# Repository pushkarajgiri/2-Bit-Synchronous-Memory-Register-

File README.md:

# 2-Bit-Synchronous-Memory-Register-
74HC00N NAND gates to demonstrate Gated D-Latch architecture and synchronized volatile data storage.

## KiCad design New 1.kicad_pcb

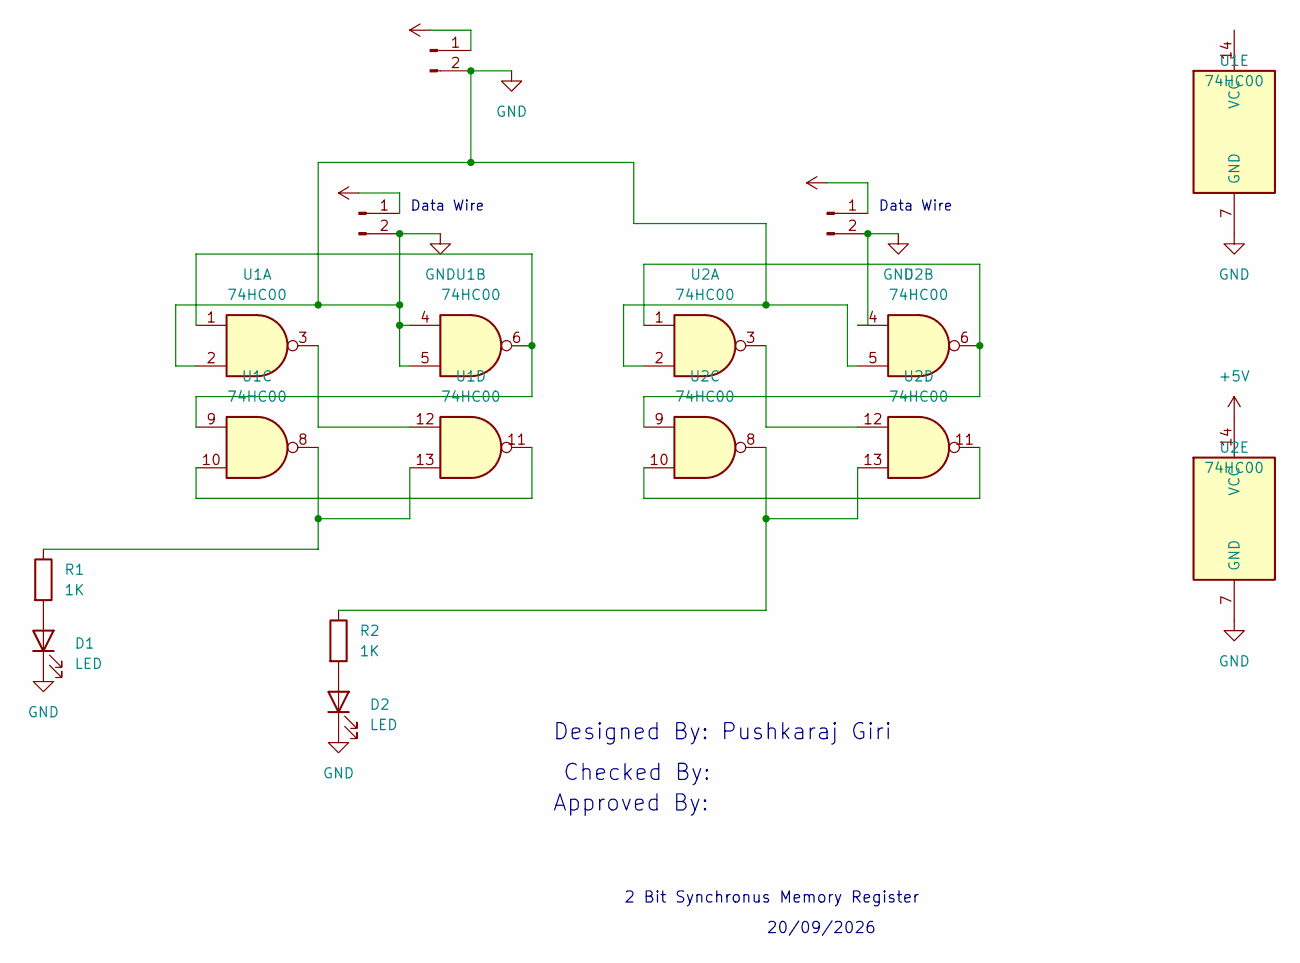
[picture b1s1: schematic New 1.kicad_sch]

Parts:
D1, D2: LED; LED_D5.0mm
J1, J2, J3: Conn_01x02_Pin; PinHeader_1x02_P2.54mm_Vertical
R1, R2: 1K; R_Axial_DIN0207_L6.3mm_D2.5mm_P10.16mm_Horizontal
U1, U2: 74HC00; DIP-14_W7.62mm

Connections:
+5V: J1.1, J2.1, J3.1, U2.14 (VCC)
GND: D1.1 (K), D2.1 (K), J1.2, J2.2, J3.2, U1.2, U1.4, U1.5, U1.7 (GND), U2.2, U2.4, U2.5, U2.7 (GND)
unnamed: D1.2 (A), R1.2
unnamed: D2.2 (A), R2.2
unnamed: R1.1, U1.8, U1.13
unnamed: R2.1, U2.8, U2.13
unnamed: U1.1, U1.6, U1.9
unnamed: U1.10, U1.11
unnamed: U1.3, U1.12
unnamed: U2.1, U2.6, U2.9
unnamed: U2.10, U2.11
unnamed: U2.3, U2.12

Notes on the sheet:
Data Wire
20/09/2026
2 Bit Synchronus Memory Register
Designed By: Pushkaraj Giri
Approved By:
Checked By:

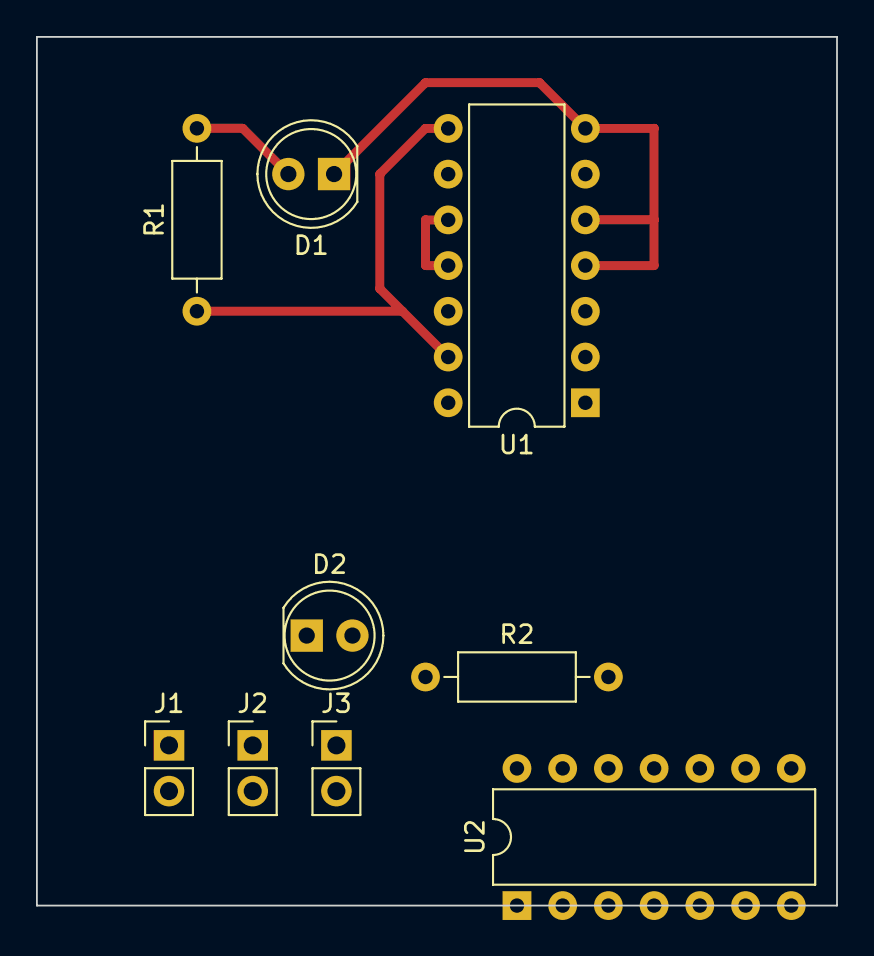
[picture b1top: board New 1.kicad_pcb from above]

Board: 2 copper layers, 44.4 x 48.3 mm, 9 parts (0 on the bottom side), 12 nets.
